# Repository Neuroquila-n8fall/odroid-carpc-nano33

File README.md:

# odroid-carpc-nano33
Derivate of odroid-carpc-due for the Arduino Nano 33 IoT
An Arduino Due project for controlling an Odroid N2 via BMW Keyfob and iDrive.

## Hardware used
- BMW 1-Series 2009
- Arduino Nano 33 IoT
- Custom board design to incoorporate MCU, Bluetooth and Canbus logic on the same board
- iDrive 7-Button Controller 
- DS18B20 Temperature Probe
- LTC3780 Power Supply Module

## Purpose
This project is intended to support an Odroid N2 in its function as a car-pc. This also involves controlling the display brightness of the Vu7+ display by applying PWM signals to its backlight chip by reacting on the cars' light sensor on the windscreen.
As a bonus it's designed to support an iDrive controller as an input device for the Odroid to have comfortable access to the car-pc functions. To make it function properly an app called "Button Mapper" is used to react on F-Keys.
See: https://play.google.com/store/apps/details?id=flar2.homebutton

## Electrical Details
The brainbox of this module is a Arduino Nano 33 IoT which has its own 3v3 voltage regulator on board. To reduce stress it is supplied by the onboard 5V regulator from Recom. This 5V supply also powers the TJA1050 controller which needs 5V in order to generate the signals on the CAN-Bus. The Bluetooth module, MCP2515 and INA219 are supplied by the Arduino's voltage regulator.

The 5V Regulator is supplied by an external power supply and tolerates a maximum of 12V.

Because of the internal wiring of the Arduino, even the Fans will work when the Arduino is powered via USB. You will read 3V on the 12V rail if only the Arduino is plugged in to a Supply via USB. I've missed to include a Schottky Diode in order to prevent this behavior but it doesn't hurt either because everything is on the same potential and the internal regulator of the Arduino can deliver 1A continously. This also enables you to diagnose things on desk without hooking up everything to a external DC supply.

### Part selection
When selecting parts I've focused to select hose which are either AECQ100 certified or have an extended operating temperature range until at least 85°C. You should select parts for automotive use to ensure they last as long as possible.
```diff
- ATTENTION: Contrary to the schematics and board, the TCMT1100 up to TCMT1102 optocouplers can be used.
The TCMT1104 requires 10mA to trigger which the SAMD21 can't deliver. It's maximum current on a pin is 7mA
```
### Fan sockets
The PWM signal is tuned to work with all fans. I've tested bog standard 120mm fans as well as a dual high-pressure cisco switch fan. Please note that the socket delivers the voltage from the 12V rail. There is no possibility to power 5V fans here.

## 3rd Party Libraries used
I'm using a modified version of the BPLib that now supports sending and holding multiple keys. That's probably important for future tweaks. The original library only supports sending one single key and modifiers.
See: https://github.com/Neuroquila-n8fall/BPLib

Also: Seeedstudios Canbus Shield library
See: https://github.com/Seeed-Studio/CAN_BUS_Shield

## Usage
### Intended Usage & prerequisites
The main key aspect of the layout is to connect an external power supply which is supplied by the battery of the car through the board. The intention behind this is to keep everything safely connected. Cars are very flammable and therefore the top priority has to be that there is no risk of loose, uninsulated wires dangling around!

A DS18B20 temperature probe is required in order to keep track of the temperatures of the pc and control the fans accordingly.

### Wiring
This new revision has everything on board which makes wiring very easy. It also minimizes the amount of wiring.

All of the terminals have a Description on the bottom which usually is hidden by the terminal itself. That's why a more descriptive text is added to the top.
You'll find a Terminal for the following auxillary devices:
- Display (VU7A+): One Output for controlling the background lighting and one for triggering the power button
- CAN-Bus: You can hook up your K-Can to the screw terminal or the pin headers behind.
- PC: This is the output for the Odroid. It receives power directly from the 12V terminal
- 12V: Power supply input from an external regulated power supply. I heavily recommend a supply board with the LTC3780 chip.
- IGN: Ignition. Two terminals are available because we only need one positive input. In case you want to hook up something on the ignition, this is the right place
- IGN-AP: Ignition output for Access Points. I'm using the Teltonika RUT850 which needs this supply in order to power up and down on itself
- BAT: Battery Input. Used by the control logic to check for voltage levels and also delivers power to the DC Supply
- PSU (BOUT): Battery Out. Intended to be used as Output to the power supply. This Terminal is switched by the "1/0" pin header between"IGN-AP2 and "BAT"
- BAT-AP: Used by the Teltonika access point as permanent supply

#### Color blocks explained
- Green: Shared 12v Rail
- Orange/Yellow: Shared Ignition Rail
- Purple: Shared Battery Rail

### Parameters
Parameters are described inside the source file "main.h" (https://github.com/Neuroquila-n8fall/odroid-carpc-nano33/blob/master/src/main.h)
Everything is well tested and works right out of the box. The prototype is already reaching one year of service on my car and shares the same code base.

### I2C
There are two solder pads "SCL-N" and "SDA-N" on the bottom to be bridged when you want to establish I2C communication between the Odroid N2 and the Arduino. This will join the N2 to the Arduino I2C bus. Important: The Arduino is the bus master!

### First-Run
#### Bluetooth Module Setup
Before uploading the sketch to the Arduino, you should head over to the setup section and uncomment the line "initalSetup()". Then, head over to the function and customize the name of the device and PIN. This will then set the required settings on the next startup of the Arduino on the bluetooth module so it works as intended. You may also use a Serial redirection sketch to enter the commands yourself or tweak things.
After that you should comment the section again and re-upload the sketch.

## Functions & Behaviour
### Startup
When you open the car by keyfob, the PC will be started by pulling down the power button GPIO pin on the Odroid for a second. This will turn on the Odroid.
### Shutdown
When you close the car by keyfob, it will pull down the GPIO pin again but now for several seconds which triggers the shutdown routine of the Odroid so it shuts down gracefully.
### Queuing
You can queue exactly one action by pressing "open" or "close" on the keyfob respectively. 

What does this mean? 

This means that if you want to take something out of the car and leave it again, you will have to press "open" and "close" in a rather short timespan. usually this would mean the startup process will be terminated or the PC will run until you enter the car again or press the "close" button again after the Pc booted up. Instead the controller stores the second action and waits for the PC to boot up and then shuts it down gracefully again. Because we never now when a "open" is followed by driving or just for accessing the car for a short duration this system prevents ungraceful shutdowns or battery drain.

Vice-Versa this means when closing the car and re-opening it again, the Odroid will be started again shortly. 
### Battery Monitoring (WIP)
- If the battery drops below a certain voltage, the Odroid will be shut down gracefully
- Fans will be shut down
- Everything else stays active. I'm planning to save energy by only enabling WiFi if the ignition is on.
### WiFi
- Wifi is included and active and intended to provide IoT functionality in the future. I have yet to think about useful scenarios where this feature comes in handy
- As of now WiFi is used to synchronize the RTC via NTP
### iDrive Controls
If an iDrive Controller is placed on the CAN Network, the controller will start to communicate with the network. The Sketch has the correct facilities in place to keep it awake and enable the rotation encoder. I've tried to resemble the original behavior of the iDrive controller.
- Rotation is scrolling up and down respectively
- Pushing the Menu button or the knob equals "Enter"
- Pushing the knob in any direction will emulate a directional arrow key so you can navigate in two dimensions between UI elements.

Things worthy of noting:
- Some apps don't come with keyboard support. Android is a touch-centric OS and therefore only a few devs implement full fledged keyboard control. Apps that work well are: Sygic, Spotify, Torque, Google Maps, Chrome
- You should use the button mapper app to implement extended features like return to home by long press and stuff like that
- Mapping buttons to apps can be done via Odroid Settings
### Multi Function Steering Wheel Buttons
Native support is integrated which means you can skip music tracks with the arrow keys and fast-forward and rewind when holding those buttons.
### Display Brightness Adjustment
The controller fetches messages from the CAN network from the RLS module (Regen Licht Sensorik) which sits, if fitted, on the windscreen behind the rearview mirror. It then maps those values to control the screen brightness of the VU7a display. The control values are proven but may vary between cars.

## Signalling & Diagnosis
There are plenty of status led on the board:
- One for the battery rail which indicates that the battery is connected
- One for the 12v rail to indicate a working power supply input
- One for the ignition rail so you know if the ignition input works
- One for the 3v3 and 5v rails 
- 2 for the bluetooth module: BTACT = Activity: Tells you what the module is doing, BTSTA = Status: Off when a device is connected
- 2 for the Arduino: STA tells you if the PC is running, ACT tells you if there is activity on the CAN-Bus and pulses when nothing is going on
- One for the fans: On if the relay is opened and fans are enabled
- There is also an optional OLED Grove connector. Because of timing issues I removed it from the project but it can be used as a diagnostical device if needed. Since 5v and I2C is supplied there, you can hook up other stuff to this port.

## Known Issues
- ~~As soon as the car battery is depleted, the arduino will write value 0 to the display brightness pin when the engine starts or doors are fully opened and closed. I have yet to understand why on earth this is happening even when the engine is already running. I can only think of a solution where the brightness is updated frequently, like 10 seconds or so.~~

**Solved: Explicit correction of values that are out of range. When the car has recovered from a very low voltage level, the light sensor reports values that are not mapped correctly by the "map" function. Such values are now being overwritten**
- ~~When the car is not shut and goes into hibernation and the car pc is still running, it might happen that the display goes dark. This might also be related to the aforementioned problem and may point to an integer overflow issue on the brightness calculation. Maybe the sensor on the windshield (RLS Control Module) sends some crazy data when it goes into hibernation.~~

**Solved: Same issue and solution as above**

- Sometimes the "restart" feature of the queuing mechanism doesn't work. Odroid will then start after the ignition is on.

- Apparently setting the PWM clock to 25kHz in order to control PWM fans also affects the display brightness pin somehow. This is something I didn't see coming. Maybe another pin configuration is needed...

## Questions I got asked...
Why all the hassle if I could just simply upgrade the car to the official iDrive?
Because I always felt the need to include a full blown car pc into my car. Upgrading to iDrive wasn't an option due to the fact that this system is just too limited. If I had a recent model, this wouldn't be a problem but sitting on a rather "old" car leaves one without options. I want a browsable music library with cloud sync, internet, the precious Torque app, ...all the good stuff!
The icing on the cake was the decision to go the extra mile and swap the center console and install an iDrive 7-Button control unit. It looks like OEM but it does much, much more.

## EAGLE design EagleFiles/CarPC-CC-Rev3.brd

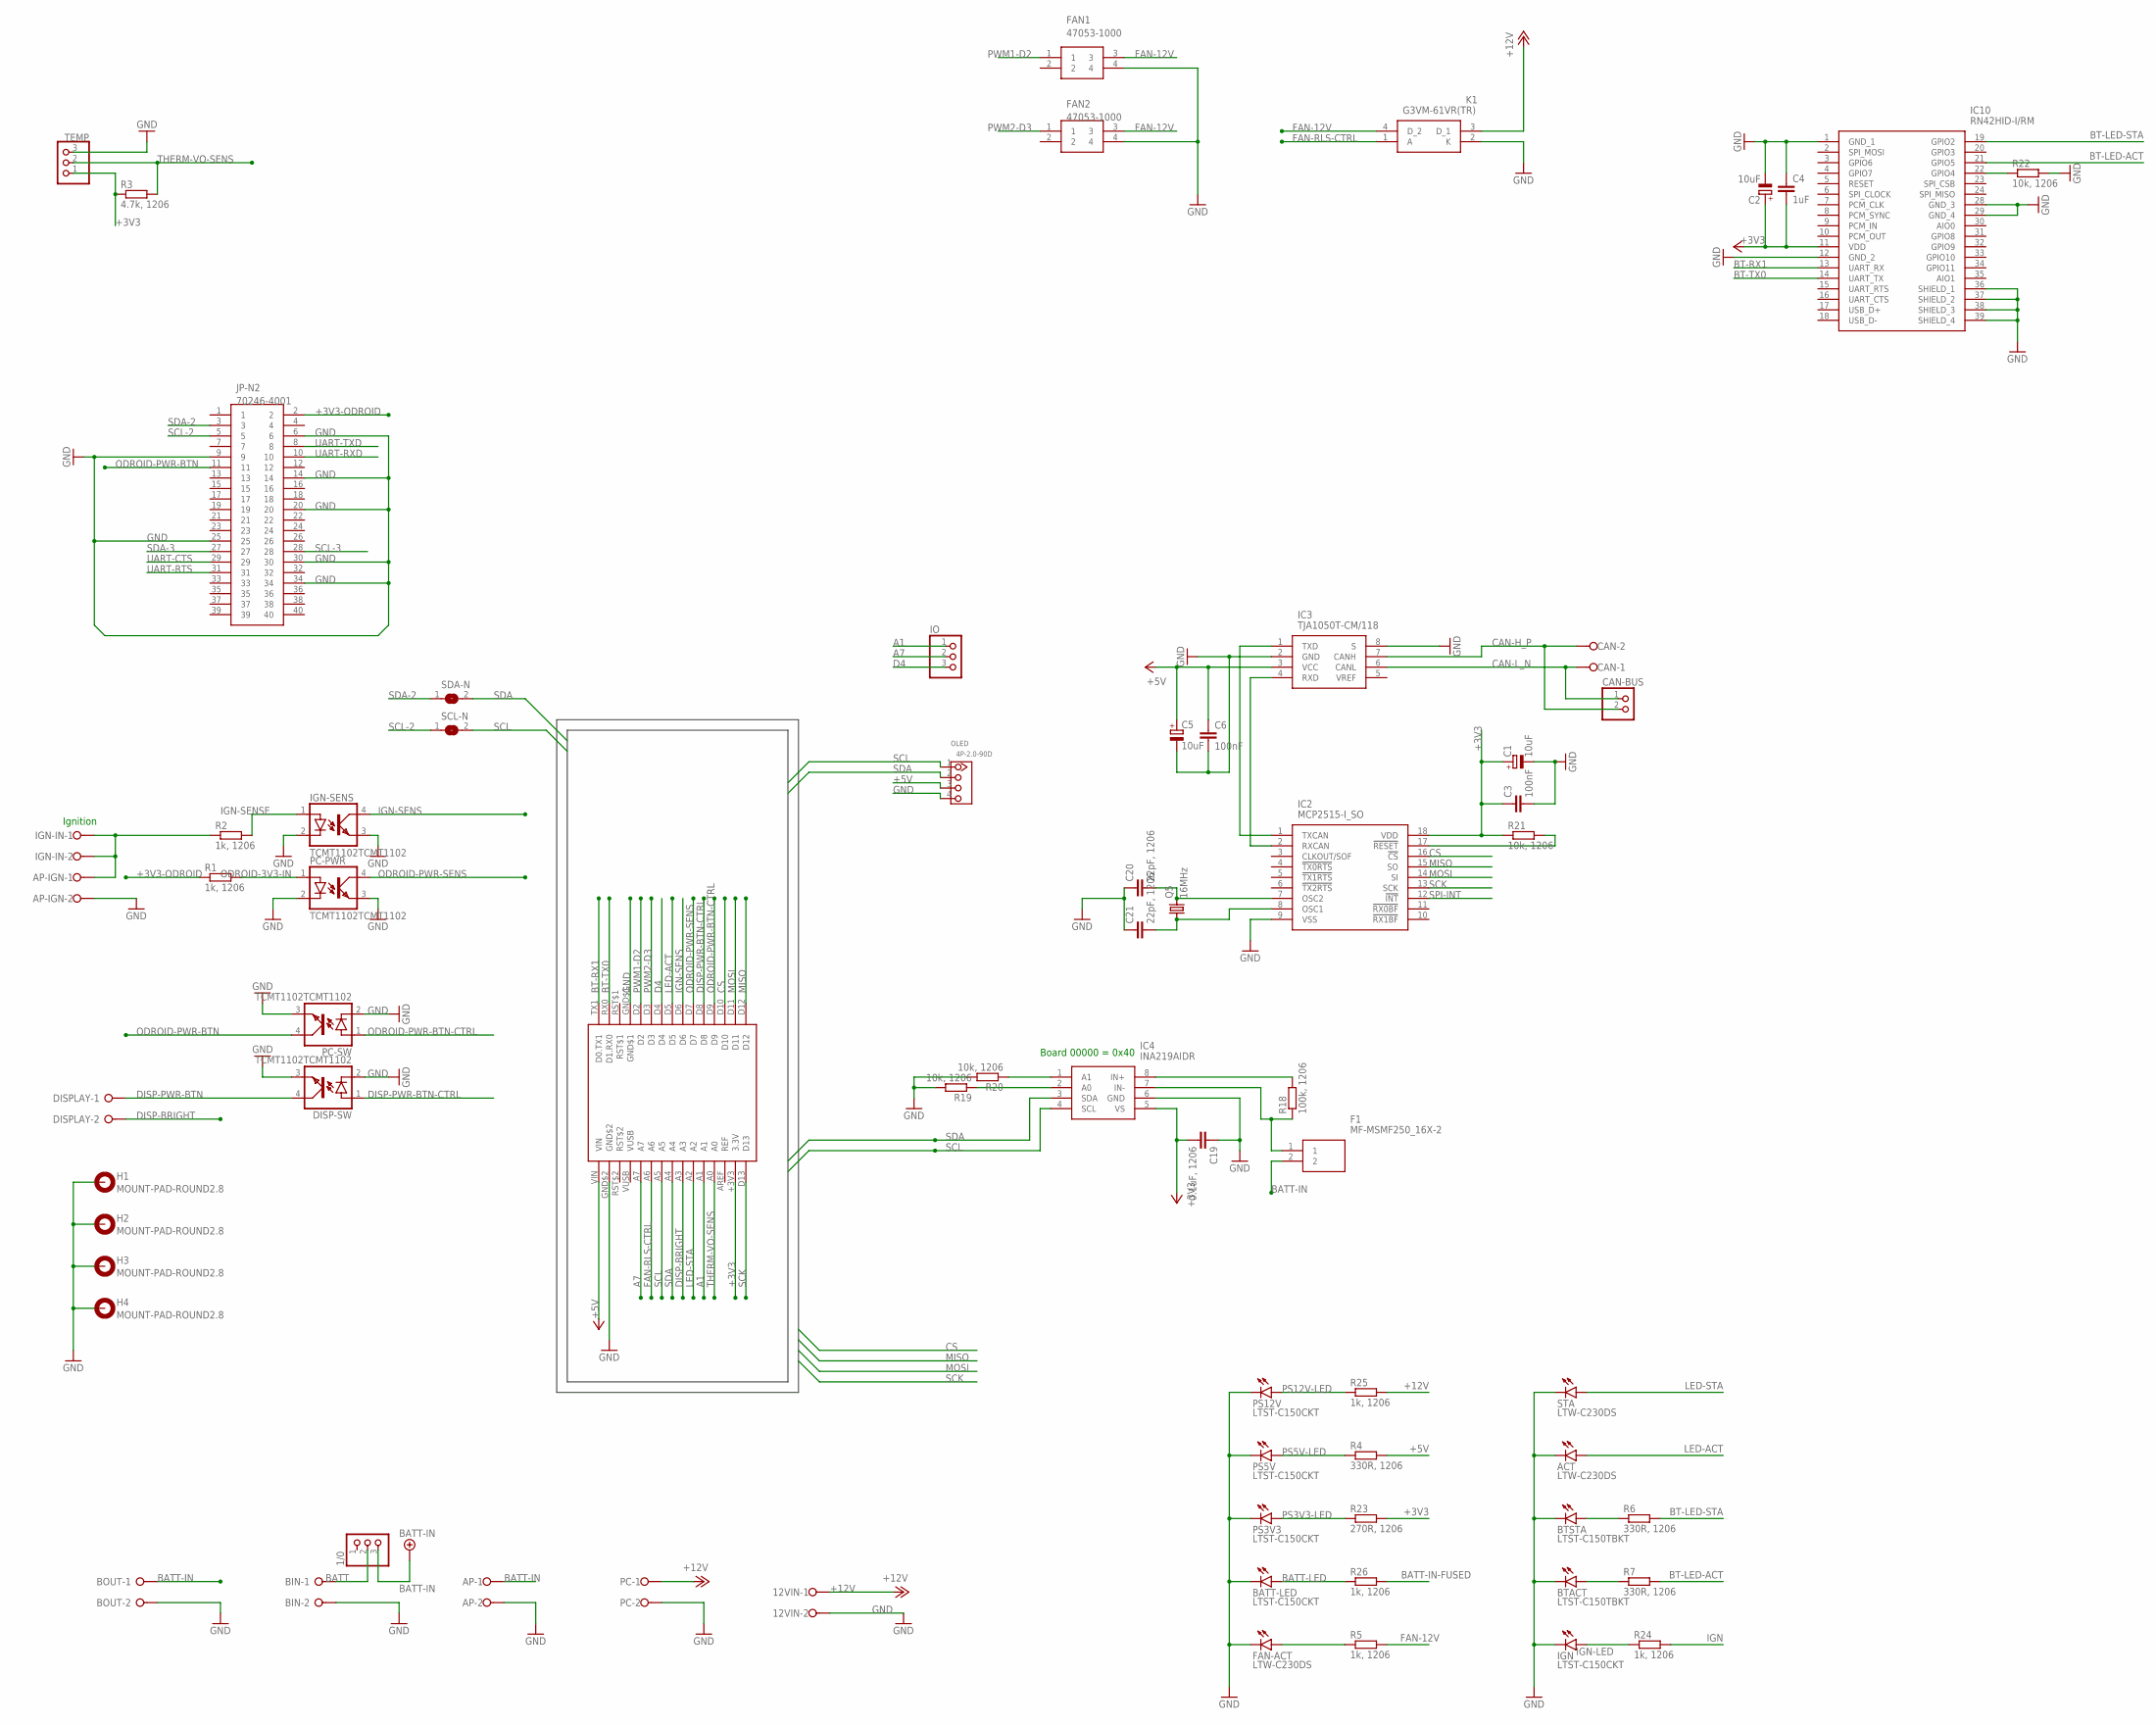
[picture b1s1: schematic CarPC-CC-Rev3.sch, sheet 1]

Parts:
1/0: PINHD-1X3; 1X03
12VIN: W237-02P; W237/132
ACT: LTW-C230DS; CHIPLED_1206
AP: W237-02P; W237/132
AP-IGN: W237-02P; W237/132
BATT-LED: LTST-C150CKT; CHIPLED_1206
BIN: W237-02P; W237/132
BOUT: W237-02P; W237/132
BTACT: LTST-C150TBKT; CHIPLED_1206
BTSTA: LTST-C150TBKT; CHIPLED_1206
C1, C2, C5: 10uF; C1206
C3, C6: 100nF; C1206
C4: 1uF; C1206
C19: 0.1uF, 1206; C1206
C20, C21: 22pF, 1206; C1206
CAN: W237-02P; W237/132
CAN-BUS: PINHD-1X2; 1X02
DISP-SW: TCMT1102TCMT1102; SOIC127P700X230-4N
DISPLAY: W237-02P; W237/132
F1: MF-MSMF250_16X-2; FUSC4632X160N
FAN1, FAN2: 47053-1000
FAN-ACT: LTW-C230DS; CHIPLED_1206
H1, H2, H3, H4: MOUNT-PAD-ROUND2.8; 2,8-PAD
IC2: MCP2515-I_SO; SOIC127P1030X265-18N
IC3: TJA1050T-CM/118; SOIC127P600X175-8N
IC4: INA219AIDR; SOIC127P600X175-8N
IC10: RN42HID-I/RM; RN42HIDIRM
IGN: LTST-C150CKT; CHIPLED_1206
IGN-IN: W237-02P; W237/132
IGN-SENS: TCMT1102TCMT1102; SOIC127P700X230-4N
IO: PINHD-1X3; 1X03
JP-N2: 70246-4001; SHDR40W94P254_2X20_5842X889X92
K1: G3VM-61VR(TR); G3VM61VRTR
NANO_33_IOT: Arduino-Nano-33-IOT; ARDNANO33IOT_SMD
OLED: 4P-2.0-90D; HW4-2.0-90D
PC: W237-02P; W237/132
PC-PWR: TCMT1102TCMT1102; SOIC127P700X230-4N
PC-SW: TCMT1102TCMT1102; SOIC127P700X230-4N
PS3V3, PS5V, PS12V: LTST-C150CKT; CHIPLED_1206
Q5: 16MHz; HC49-S
R1, R2, R5, R24, R25, R26: 1k, 1206; R1206
R3: 4.7k, 1206; R1206
R4, R6, R7: 330R, 1206; R1206
R18: 100k, 1206; R1206
R19, R20, R21, R22: 10k, 1206; R1206
R23: 270R, 1206; R1206
SCL-N: SJ
SDA-N: SJ
STA: LTW-C230DS; CHIPLED_1206
TEMP: PINHD-1X3/90; 1X03/90

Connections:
+3V3: C1.1 (+), C2.1 (+), C3.1, C4.2, C19.2, IC2.18 (VDD), IC4.5 (VS), IC10.11 (VDD), NANO_33_IOT.+3V3 (3.3V), R3.1, R21.1, R23.2, TEMP.1
+3V3-ODROID: JP-N2.2, R1.1
+5V: C5.1 (+), C6.1, IC3.3 (VCC), NANO_33_IOT.VIN, OLED.3, R4.2; also elsewhere on the board
+12V: 12VIN.1, K1.3 (D_1), PC.1, R25.2; also elsewhere on the board
A1: IO.1, NANO_33_IOT.A1
A7: IO.2, NANO_33_IOT.A7
BATT: 1/0.2, BIN.1
BATT-IN: 1/0.3, AP.1, BOUT.1, F1.2
BATT-IN-FUSED: F1.1, IC4.7 (IN-), R18.1, R26.2
BATT-LED: BATT-LED.A, R26.1
BT-ACTIVATE: IC10.22 (GPIO4), R22.1
BT-LED-ACT: IC10.21 (GPIO5), R7.2
BT-LED-STA: IC10.19 (GPIO2), R6.2
BT-RX1: IC10.13 (UART_RX), NANO_33_IOT.TX1 (D0.TX1)
BT-TX0: IC10.14 (UART_TX), NANO_33_IOT.RX0 (D1.RX0)
CAN-H_P: CAN.2, CAN-BUS.2, IC3.7 (CANH)
CAN-L_N: CAN.1, CAN-BUS.1, IC3.6 (CANL)
CS: IC2.16 (!CS), NANO_33_IOT.D10
D4: IO.3, NANO_33_IOT.D4
DISP-BRIGHT: DISPLAY.2, NANO_33_IOT.A3
DISP-PWR-BTN: DISP-SW.4 (COL), DISPLAY.1
DISP-PWR-BTN-CTRL: DISP-SW.1 (A), NANO_33_IOT.D8
FAN-12V: FAN1.3, FAN2.3, K1.4 (D_2), R5.2
FAN-RLS-CTRL: K1.1 (A), NANO_33_IOT.A6
GND: 12VIN.2, ACT.C, AP.2, AP-IGN.2, BATT-LED.C, BIN.2, BOUT.2, BTACT.C, BTSTA.C, C1.2 (-), C2.2 (-), C3.2, C4.1, C5.2 (-), C6.2, C19.1, C20.1, C21.1, DISP-SW.2 (K), DISP-SW.3 (EMI), FAN1.4, FAN2.4, FAN-ACT.C, H1.B2,8, H2.B2,8, H3.B2,8, H4.B2,8, IC2.9 (VSS), IC3.2 (GND), IC3.8 (S), IC4.6 (GND), IC10.1 (GND_1), IC10.12 (GND_2), IC10.28 (GND_3), IC10.29 (GND_4), IC10.36 (SHIELD_1), IC10.37 (SHIELD_2), IC10.38 (SHIELD_3), IC10.39 (SHIELD_4), IGN.C, IGN-SENS.2 (K), IGN-SENS.3 (EMI), JP-N2.6, JP-N2.9, JP-N2.14, JP-N2.20, JP-N2.25, JP-N2.30, JP-N2.34, K1.2 (K), NANO_33_IOT.GND$1, NANO_33_IOT.GND$2, OLED.4, PC.2, PC-PWR.2 (K), PC-PWR.3 (EMI), PC-SW.2 (K), PC-SW.3 (EMI), PS3V3.C, PS5V.C, PS12V.C, R19.2, R20.2, R22.2, STA.C, TEMP.3; also elsewhere on the board
IGN: AP-IGN.1, IGN-IN.1, IGN-IN.2, R2.1, R24.2
IGN-LED: IGN.A, R24.1
IGN-SENS: IGN-SENS.4 (COL), NANO_33_IOT.D6
IGN-SENSE: IGN-SENS.1 (A), R2.2
INA-0X40-ADDR0: IC4.2 (A0), R19.1
INA-0X40-ADDR1: IC4.1 (A1), R20.1
LED-ACT: ACT.A, NANO_33_IOT.D5
LED-STA: NANO_33_IOT.A2, STA.A
MCP-OSC1: C21.2, IC2.8 (OSC1), Q5.1
MCP-OSC2: C20.2, IC2.7 (OSC2), Q5.2
MCP-RESET: IC2.17 (!RESET), R21.2
MCP-TJA-RX: IC2.2 (RXCAN), IC3.4 (RXD)
MCP-TJA-TX: IC2.1 (TXCAN), IC3.1 (TXD)
MISO: IC2.15 (SO), NANO_33_IOT.D12
MOSI: IC2.14 (SI), NANO_33_IOT.D11
unnamed: FAN-ACT.A, R5.1
unnamed: BTSTA.A, R6.1
unnamed: BTACT.A, R7.1
ODROID-3V3-IN: PC-PWR.1 (A), R1.2
ODROID-PWR-BTN: JP-N2.11, PC-SW.4 (COL)
ODROID-PWR-BTN-CTRL: NANO_33_IOT.D9, PC-SW.1 (A)
ODROID-PWR-SENS: NANO_33_IOT.D7, PC-PWR.4 (COL)
PS3V3-LED: PS3V3.A, R23.1
PS5V-LED: PS5V.A, R4.1
PS12V-LED: PS12V.A, R25.1
PWM1-D2: FAN1.1, NANO_33_IOT.D2
PWM2-D3: FAN2.1, NANO_33_IOT.D3
SCK: IC2.13 (SCK), NANO_33_IOT.D13
SCL: IC4.4 (SCL), NANO_33_IOT.A5, OLED.1, SCL-N.2
SCL-2: JP-N2.5, SCL-N.1
SCL-3: JP-N2.28
SDA: IC4.3 (SDA), NANO_33_IOT.A4, OLED.2, SDA-N.2
SDA-2: JP-N2.3, SDA-N.1
SDA-3: JP-N2.27
SHUNT+: IC4.8 (IN+), R18.2
SPI-INT: IC2.12 (!INT)
THERM-VO-SENS: NANO_33_IOT.A0, R3.2, TEMP.2
UART-CTS: JP-N2.29
UART-RTS: JP-N2.31
UART-RXD: JP-N2.10
UART-TXD: JP-N2.8

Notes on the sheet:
Ignition
Board 00000 = 0x40

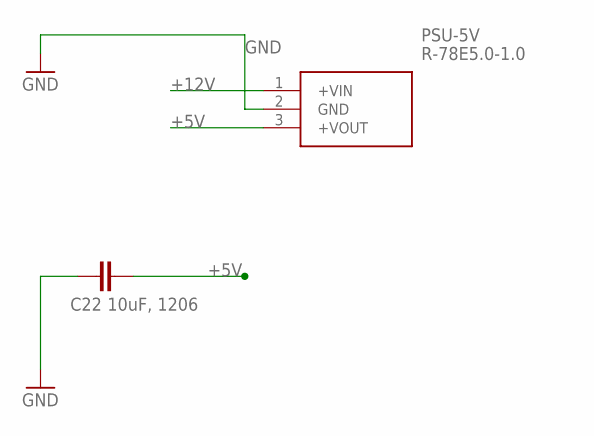
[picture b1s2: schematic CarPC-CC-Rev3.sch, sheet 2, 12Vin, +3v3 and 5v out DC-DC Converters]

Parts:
C22: 10uF, 1206; C1206
PSU-5V: R-78E5.0-1.0

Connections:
+5V: C22.2, PSU-5V.3 (+VOUT); also elsewhere on the board
+12V: PSU-5V.1 (+VIN); also elsewhere on the board
GND: C22.1, PSU-5V.2 (GND); also elsewhere on the board

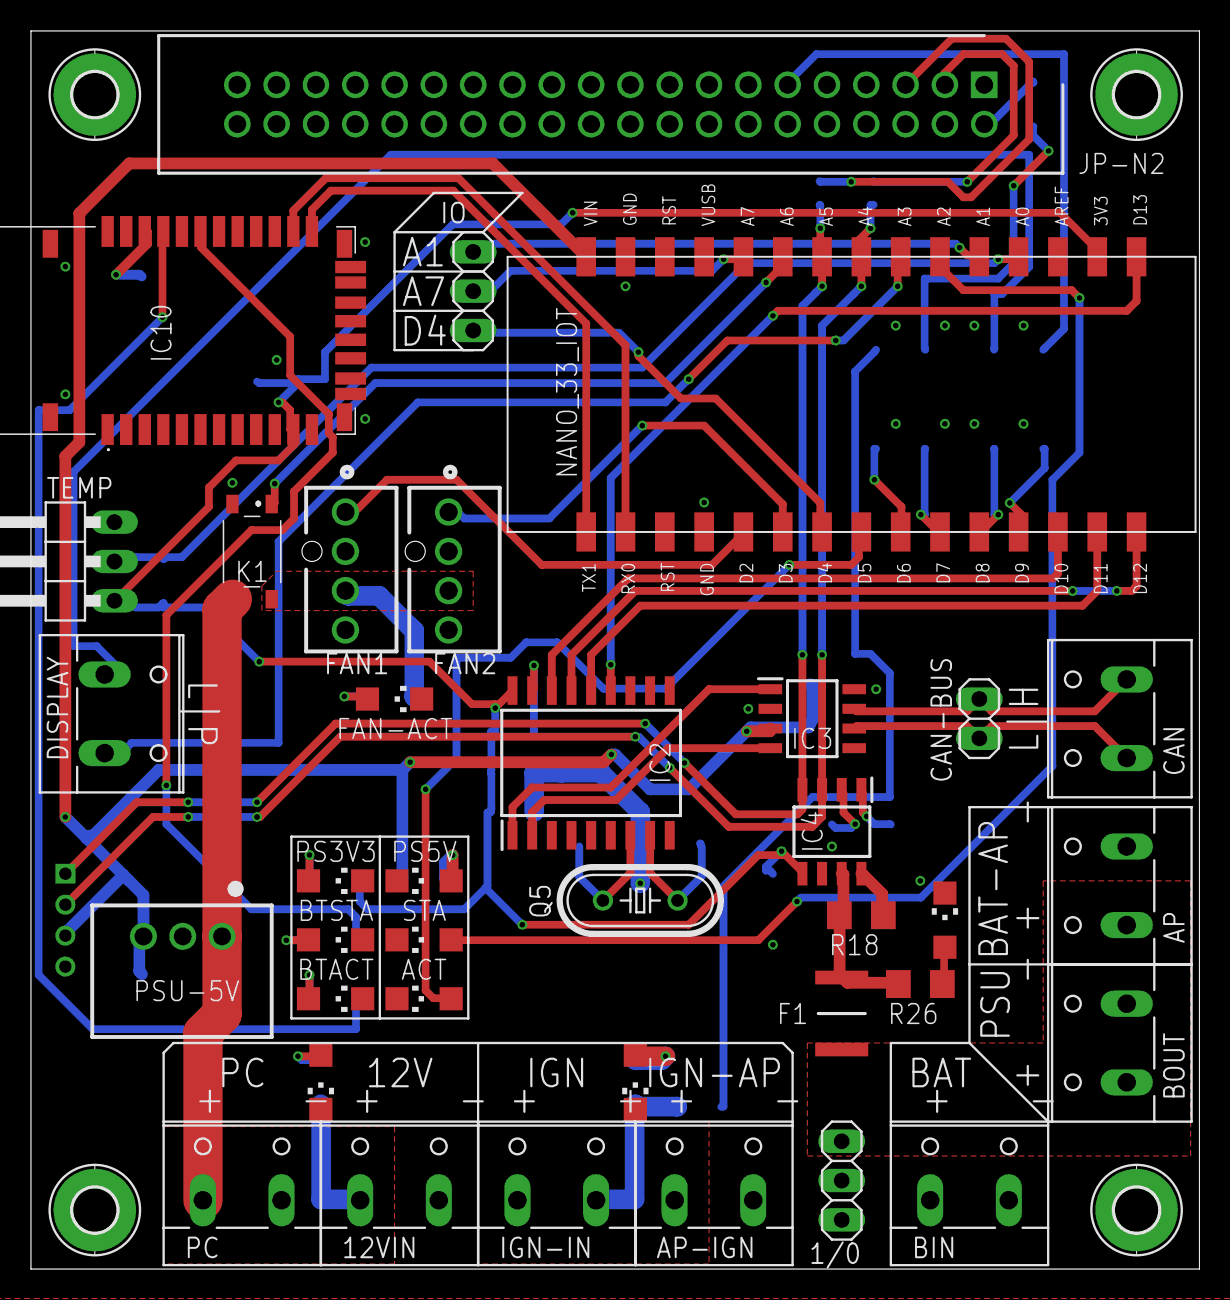
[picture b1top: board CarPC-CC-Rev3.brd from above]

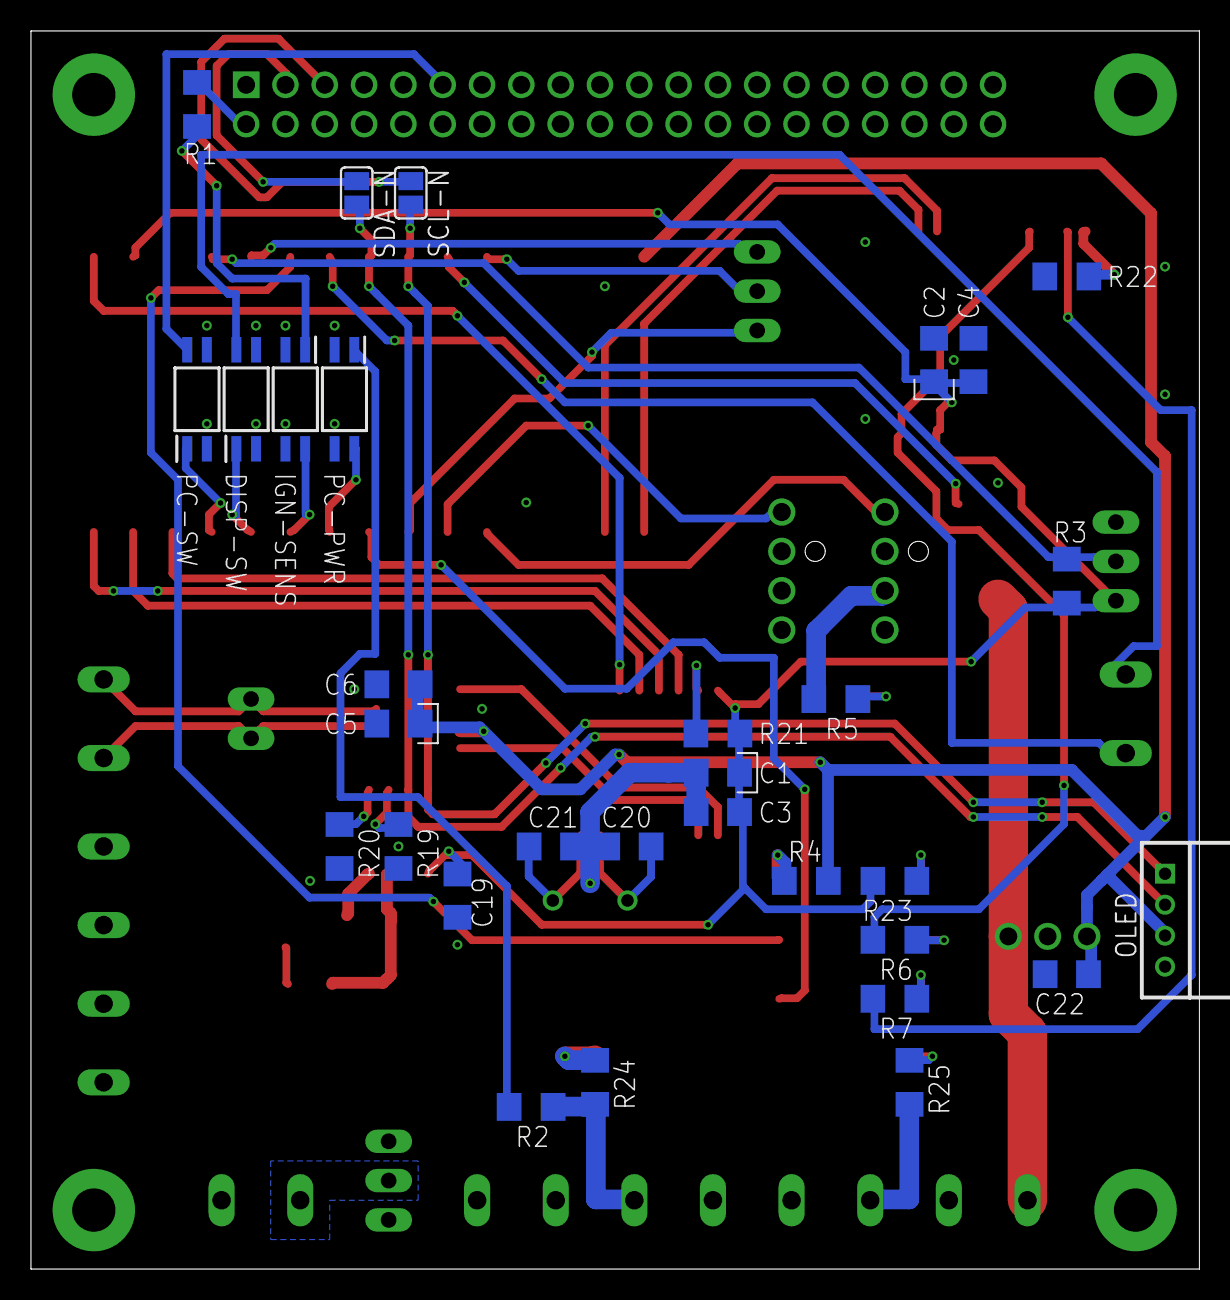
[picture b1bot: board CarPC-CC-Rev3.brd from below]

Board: 2 copper layers, 75.5 x 80.0 mm, 72 parts (31 on the bottom side), 59 nets.

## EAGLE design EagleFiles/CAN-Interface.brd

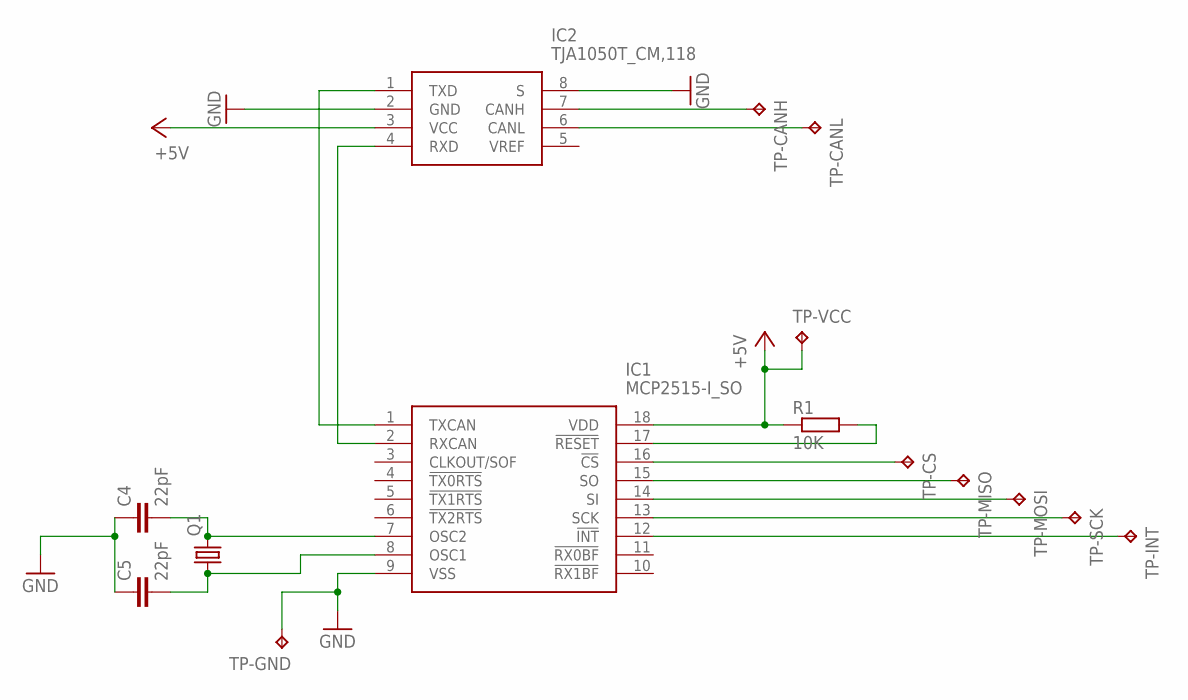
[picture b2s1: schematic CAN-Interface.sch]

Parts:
C4, C5: 22pF; C025-050X050
IC1: MCP2515-I_SO; SOIC127P1030X265-18N
IC2: TJA1050T_CM,118; SOIC127P600X175-8N
Q1: CRYSTALHC49S; HC49/S
R1: 10K; 0204/7
TP-CANH: TPB1,27; B1,27
TP-CANL: TPB1,27; B1,27
TP-CS: TPB1,27; B1,27
TP-GND: TPB1,27; B1,27
TP-INT: TPB1,27; B1,27
TP-MISO: TPB1,27; B1,27
TP-MOSI: TPB1,27; B1,27
TP-SCK: TPB1,27; B1,27
TP-VCC: TPB1,27; B1,27

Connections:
+5V: IC1.18 (VDD), IC2.3 (VCC), R1.1, TP-VCC.TP
GND: C4.1, C5.1, IC1.9 (VSS), IC2.2 (GND), IC2.8 (S), TP-GND.TP
unnamed: C4.2, IC1.7 (OSC2), Q1.2
unnamed: C5.2, IC1.8 (OSC1), Q1.1
unnamed: IC2.7 (CANH), TP-CANH.TP
unnamed: IC2.6 (CANL), TP-CANL.TP
unnamed: IC1.16 (!CS), TP-CS.TP
unnamed: IC1.15 (SO), TP-MISO.TP
unnamed: IC1.14 (SI), TP-MOSI.TP
unnamed: IC1.17 (!RESET), R1.2
unnamed: IC1.1 (TXCAN), IC2.1 (TXD)
unnamed: IC1.2 (RXCAN), IC2.4 (RXD)
unnamed: IC1.13 (SCK), TP-SCK.TP
unnamed: IC1.12 (!INT), TP-INT.TP

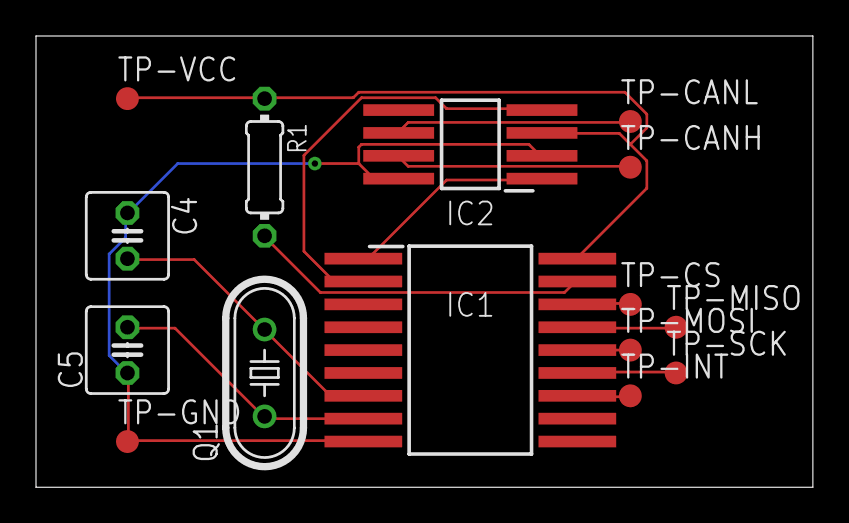
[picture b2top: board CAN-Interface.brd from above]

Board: 2 copper layers, 43.2 x 25.1 mm, 15 parts (0 on the bottom side), 14 nets.
